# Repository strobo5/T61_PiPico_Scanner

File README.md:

Keyboard scanner for a Thinkpad T61 keyboard, using the original connector,
salvaged from a retired T61, and a Raspberry Pi Pico H. Components on the BOM:

* 1x Molex 54363-0489 (WM6787CT-ND on Digikey)
* 1x Raspberry Pi Pico (with or without headers)
* 1x capacitor SMD 0603 2.2 uF
* 1x capacitor SMD 0603 100 nF
* 1x p-MOSFET TSM2305CX or similar (optional, for external 5V, e.g. a battery)
* 2x n-MOSFET 2N7002 or similar
* 4x resistor SMD 0603 10 kOhm
* 1x resistor SMD 0603 22 kOhm

Based on work by thedalles77 (schematics) and WarhawkCZ (QMK variant). HDR also
had the same idea of having the keyboard connector and the MCU module on
opposite sides to save space.
- https://github.com/thedalles77/USB_Laptop_Keyboard_Controller/tree/master/Example_Keyboards/Lenovo_ThinkPad_T61/Teensy%20LC
- https://forum.thinkpads.com/viewtopic.php?t=134293
- https://github.com/HDR/USB_Laptop_Keyboard_Controller

Thanks @tpcware for the KiCad symbol, footprint and 3D model for the Raspberry
Pi Pico. I butchered the footprint to get a THT-only variant.
https://github.com/ncarandini/KiCad-RP-Pico

Good advice came from thedalles77 on instructables to lay out the connections
on a piece of paper before assigning the nets in the schematic editor.
https://www.instructables.com/How-to-Make-a-USB-Laptop-Keyboard-Controller/

When using a Pico W it might be possible to extend this with Bluetooth, hence
the solder pads for wires to an external battery charger + 5V converter. This
might not work too well though; the keyboard's bottom is a metal shield that
probably kills the wireless transmission when the Pico W is right underneath.

Ordered on JLCPCB. The via size (0.5 mm hole, 1.1 mm overall diameter) is small
enough and does not cost extra.

The 0.5 mm drills and vias could be done by hand (with wire soldered through
the hole) if making the PCB at home.

## Third-party components

The following components in this repository are not my work:

Symbols:

* AA01B-S040VA1 - probably by Jiri Panacek (WarhawkCZ)
* Molex_54363-0489:543630489 - Copyright held by EMA Design Automation, ® Inc., all rights reserved

Footprints:

* T61_Kb_Scanner:RPi_Pico_H - adapted from the one by @tpcware
* T61_Kb_Scanner:AA01B-S040VA1 - unknown
* T61_Kb_Scanner:WM6787CT-ND - unknown
* Molex_54363-0489:CON_543630489 - Copyright held by EMA Design Automation, ® Inc., all rights reserved

## License

Copyright 2023-2024 Michael Büchler
SPDX-License-Identifier: Apache-2.0 WITH SHL-2.1

The schematics and PCB design in this repository shall use the Solderpad Hardware License v 2.1 (the “License”); you may not use this file except in compliance with the License, or, at your option, the Apache License version 2.0. You may obtain a copy of the License at

https://solderpad.org/licenses/SHL-2.1/

Unless required by applicable law or agreed to in writing, any work distributed under the License is distributed on an “AS IS” BASIS, WITHOUT WARRANTIES OR CONDITIONS OF ANY KIND, either express or implied. See the License for the specific language governing permissions and limitations under the License.

## Images

The keyboard case in the picture is this one:
https://www.printables.com/model/877321-thinkpad-t61-keyboard-base

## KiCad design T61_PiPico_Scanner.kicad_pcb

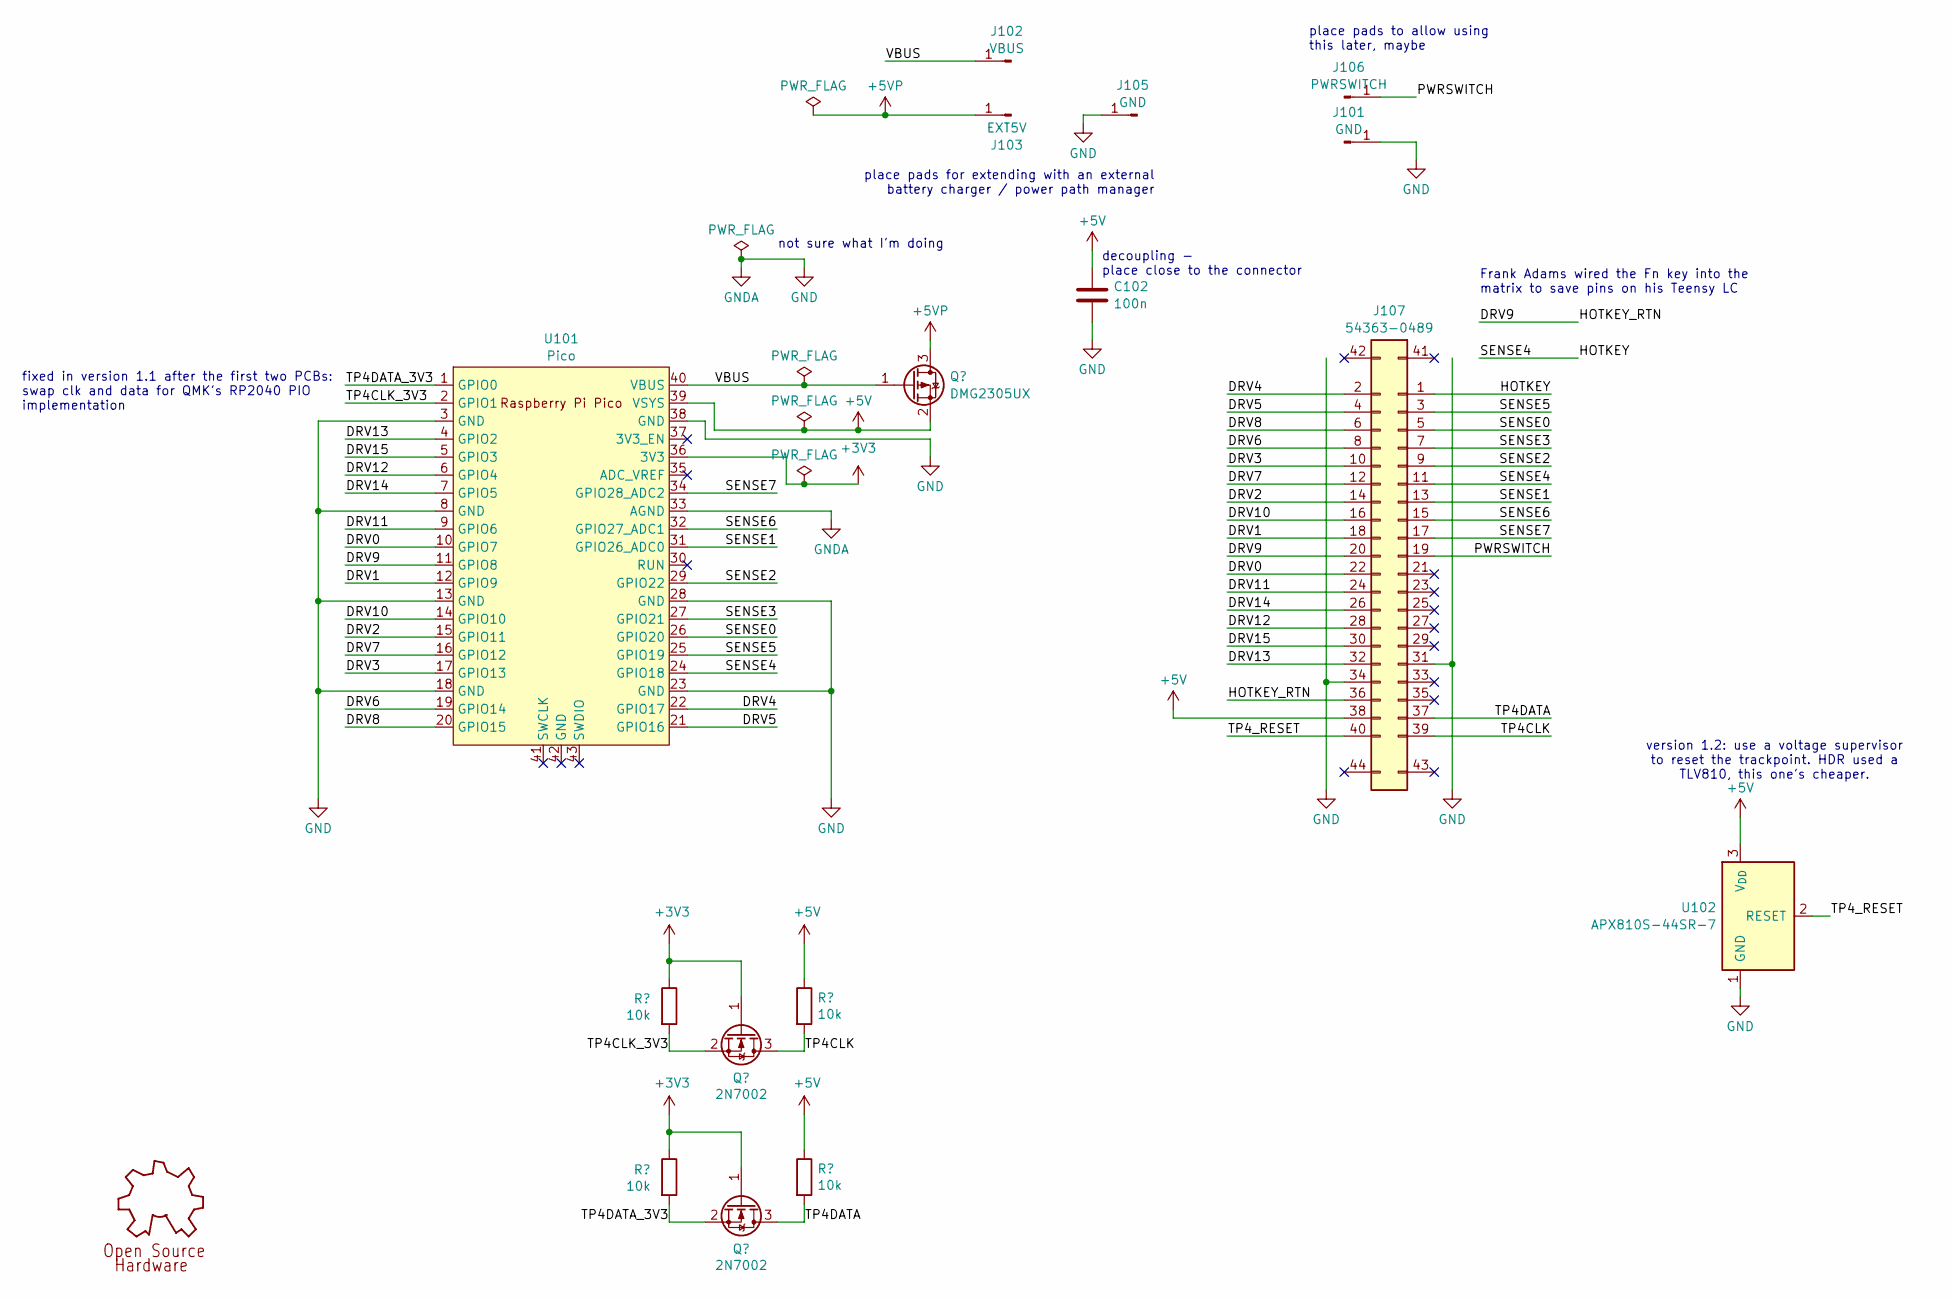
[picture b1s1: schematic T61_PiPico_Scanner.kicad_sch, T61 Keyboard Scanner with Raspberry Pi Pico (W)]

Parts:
C102: 100n; C_0603_1608Metric
GOLD_ORB_SM101: OSHWLOGOLOGO5MM; OSHW-Logo_5.7x6mm_Copper
J101, J105: GND; SolderWirePad_1x01_SMD_1x2mm
J102: VBUS; SolderWirePad_1x01_SMD_1x2mm
J103: EXT5V; SolderWirePad_1x01_SMD_1x2mm
J106: PWRSWITCH; SolderWirePad_1x01_SMD_1x2mm
J107: 54363-0489; CON_543630489_var
Q101, Q102: 2N7002; SOT-23
Q103: DMG2305UX; SOT-23
R104, R105, R106, R107: 10k; R_0603_1608Metric
U101: Pico; RPi_Pico_SMD_TH
U102: APX810S-44SR-7; SOT-23

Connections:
+3V3: Q101.1 (G), Q102.1 (G), R104.1, R105.1, U101.36 (3V3)
+5V: C102.1, J107.38, Q103.2 (S), R106.1, R107.1, U101.39 (VSYS), U102.3 (V_{DD})
+5VP: J103.1, Q103.3 (D)
/DRV0: J107.22, U101.10 (GPIO7)
/DRV1: J107.18, U101.12 (GPIO9)
/DRV2: J107.14, U101.15 (GPIO11)
/DRV3: J107.10, U101.17 (GPIO13)
/DRV4: J107.2, U101.22 (GPIO17)
/DRV5: J107.4, U101.21 (GPIO16)
/DRV6: J107.8, U101.19 (GPIO14)
/DRV7: J107.12, U101.16 (GPIO12)
/DRV8: J107.6, U101.20 (GPIO15)
/DRV9: J107.20, J107.36, U101.11 (GPIO8)
/DRV10: J107.16, U101.14 (GPIO10)
/DRV11: J107.24, U101.9 (GPIO6)
/DRV12: J107.28, U101.6 (GPIO4)
/DRV13: J107.32, U101.4 (GPIO2)
/DRV14: J107.26, U101.7 (GPIO5)
/DRV15: J107.30, U101.5 (GPIO3)
/HOTKEY: J107.1, J107.11, U101.24 (GPIO18)
/PWRSWITCH: J106.1, J107.19
/SENSE0: J107.5, U101.26 (GPIO20)
/SENSE1: J107.13, U101.31 (GPIO26_ADC0)
/SENSE2: J107.9, U101.29 (GPIO22)
/SENSE3: J107.7, U101.27 (GPIO21)
/SENSE5: J107.3, U101.25 (GPIO19)
/SENSE6: J107.15, U101.32 (GPIO27_ADC1)
/SENSE7: J107.17, U101.34 (GPIO28_ADC2)
/TP4CLK: J107.39, Q101.3 (D), R106.2
/TP4CLK_3V3: Q101.2 (S), R104.2, U101.2 (GPIO1)
/TP4DATA: J107.37, Q102.3 (D), R107.2
/TP4DATA_3V3: Q102.2 (S), R105.2, U101.1 (GPIO0)
/TP4_RESET: J107.40, U102.2 (RESET)
/VBUS: J102.1, Q103.1 (G), U101.40 (VBUS)
GND: C102.2, J101.1, J105.1, J107.31, J107.34, U101.3 (GND), U101.8 (GND), U101.13 (GND), U101.18 (GND), U101.23 (GND), U101.28 (GND), U101.33 (AGND), U101.38 (GND), U102.1 (GND)

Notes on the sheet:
decoupling - place close to the connector
place pads to allow using this later, maybe
fixed in version 1.1 after the first two PCBs: swap clk and data for QMK's RP2040 PIO implementation
place pads for extending with an external battery charger / power path manager
Frank Adams wired the Fn key into the matrix to save pins on his Teensy LC
version 1.2: use a voltage supervisor to reset the trackpoint. HDR used a TLV810, this one's cheaper.
not sure what I'm doing

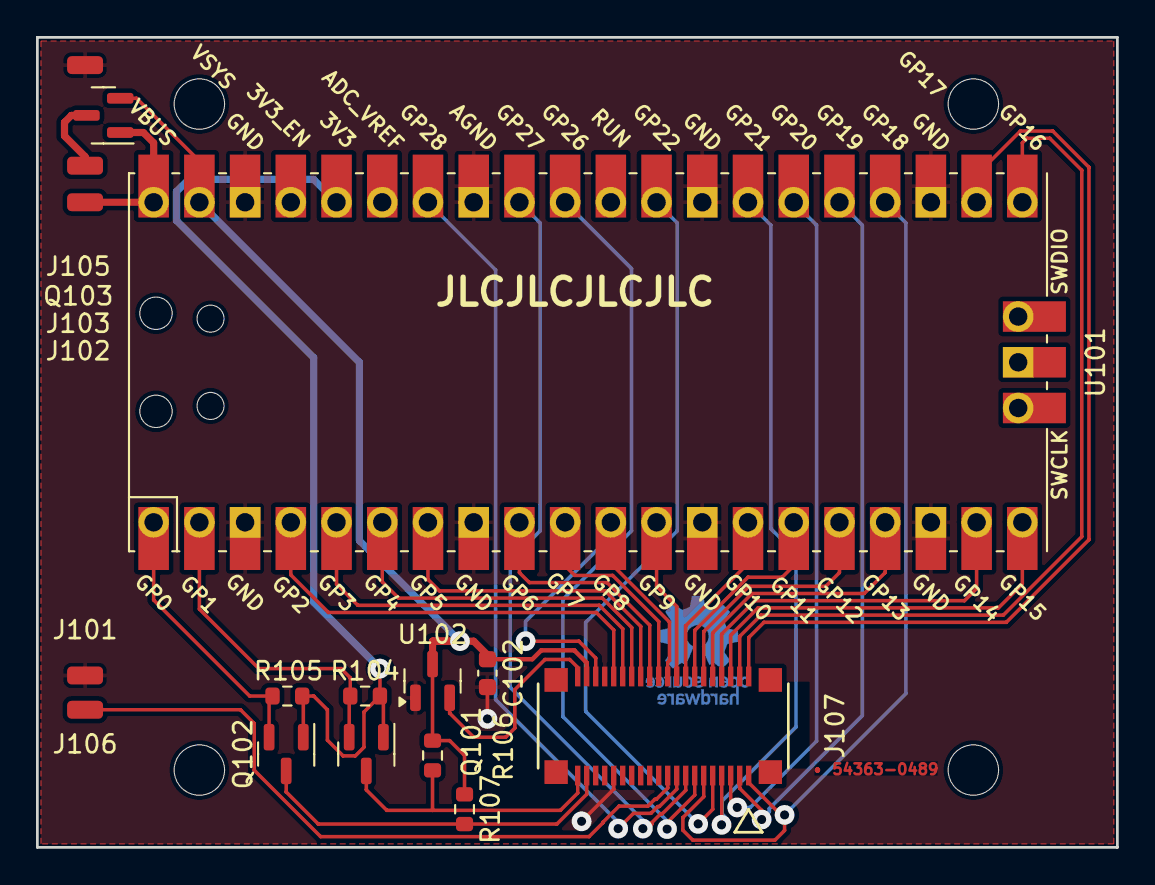
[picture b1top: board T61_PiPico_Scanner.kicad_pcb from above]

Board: 2 copper layers, 60.0 x 45.0 mm, 21 parts (1 on the bottom side), 35 nets.

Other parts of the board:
@HOLE0, @HOLE1, @HOLE2, @HOLE3: (no value)

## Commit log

2024-05-12 rev 1.1: swap PS/2 clk and data for QMK's RP2040 PIO implementation
    The only two boards with the wrong order were fixed manually.
2024-05-12 Add images and link to the case 3D file
2024-08-24 Re-write project-local symbols and footprints
2024-08-25 Add Molex 0543630489 connector
    Downloaded from UltraLibrarian through the Molex product page. See
    copyright information in the README.
2024-08-25 version 1.2: reset IC; Molex 54363-0489
2024-11-29 version 2.0: use SMT version of Pi Pico
    Now use two layers to allow keyboard connector and Pi Pico to both be on
    the top side.
    Mechanically incompatible (connector position / mounting holes) but
    electrically identical to version 1, i.e. the (QMK) firmware can stay
    the same.

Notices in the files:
T61_PiPico_Scanner.kicad_pcb:
Raspberry Pi Pico variant © Michael Büchler
Licensed under the Solderpad Hardware License v 2.1
